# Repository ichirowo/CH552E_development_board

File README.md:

## CH552E development board

This is a development board with [CH552E](http://www.wch-ic.com/products/CH552.html) from Jiangsu Haoheng Co.

It is a multi-functional microcontroller with 4 GPIO pins and supports ADC, PWM, UART, SPI, and USB targets.

LED is connected to P1.4 pin.

A boot button is provided to boot in write mode.

USB TYPE-C connector is used.

If a pin header is attached, it can be used for prototyping on a breadboard.

This board was created with Kicad version 5.1.9.

----

### License

This project is licensed as MIT License.

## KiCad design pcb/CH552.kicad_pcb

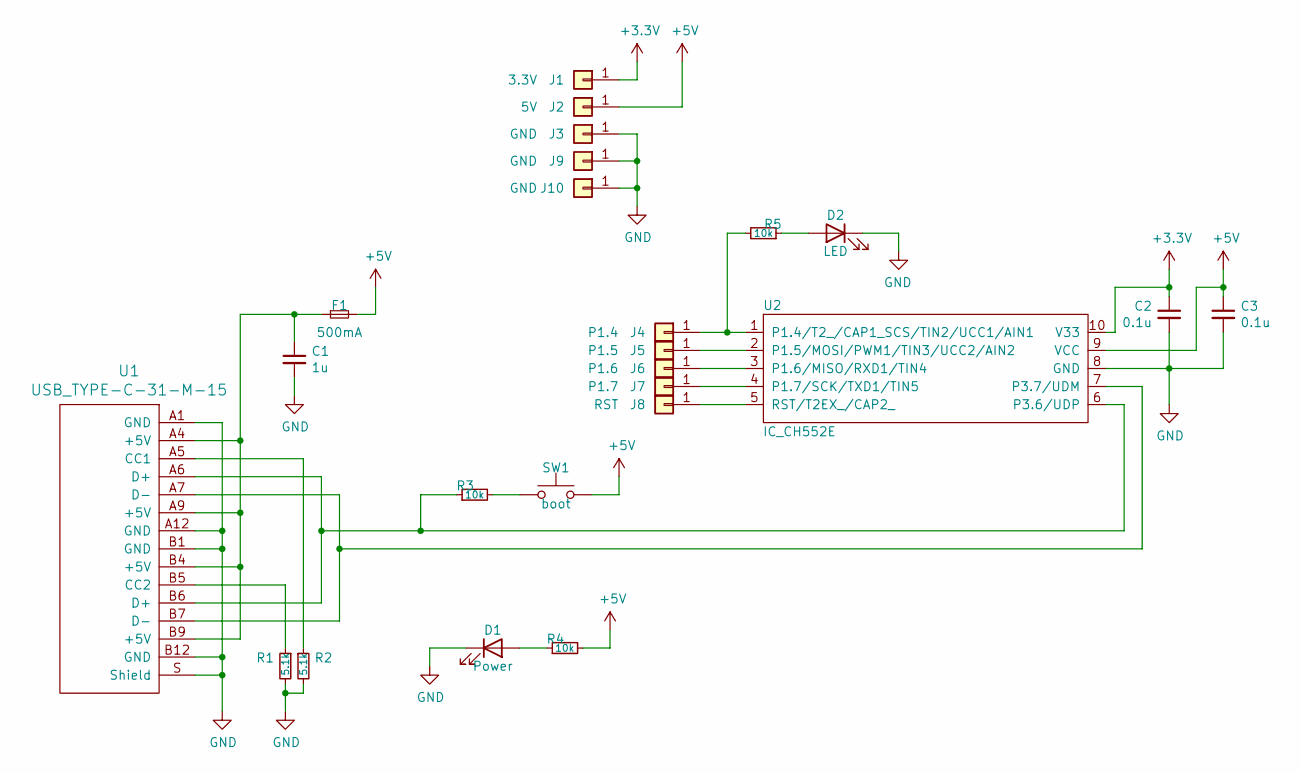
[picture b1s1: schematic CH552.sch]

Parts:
C1: 1u; C_0603_1608Metric_Pad1.05x0.95mm_HandSolder
C2, C3: 0.1u; C_0603_1608Metric_Pad1.05x0.95mm_HandSolder
D1: Power; LED_0603_1608Metric_Pad1.05x0.95mm_HandSolder
D2: LED; LED_0603_1608Metric_Pad1.05x0.95mm_HandSolder
F1: 500mA; Fuse_0603_1608Metric_Pad1.05x0.95mm_HandSolder
J1: 3.3V; Pad_1P_1.9-1.0
J2: 5V; Pad_1P_1.9-1.0
J3, J9, J10: GND; Pad_1P_1.9-1.0
J4: P1.4; Pad_1P_1.9-1.0
J5: P1.5; Pad_1P_1.9-1.0
J6: P1.6; Pad_1P_1.9-1.0
J7: P1.7; Pad_1P_1.9-1.0
J8: RST; Pad_1P_1.9-1.0
R1, R2: 5.1k; R_0603_1608Metric_Pad0.98x0.95mm_HandSolder
R3, R4, R5: 10k; R_0603_1608Metric_Pad0.98x0.95mm_HandSolder
SW1: boot; PTS810_SJM_250_SMTR_LFS
U1: USB_TYPE-C-31-M-15; USB-C_TYPE-C-31-M-12
U2: IC_CH552E; MSOP-10_3x3mm_P0.5mm

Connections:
+3V3: C2.1, J1.1, U2.10 (V33)
+5V: C3.1, F1.2, J2.1, R4.2, SW1.2, U2.9 (VCC)
GND: C1.2, C2.2, C3.2, D1.1 (K), D2.1 (K), J3.1, J9.1, J10.1, R1.2, R2.2, U1.A1 (GND), U1.A12 (GND), U1.B1 (GND), U1.B12 (GND), U1.S (Shield), U2.8 (GND)
unnamed: C1.1, F1.1, U1.A4 (+5V), U1.A9 (+5V), U1.B4 (+5V), U1.B9 (+5V)
unnamed: D1.2 (A), R4.1
unnamed: D2.2 (A), R5.1
unnamed: J4.1, R5.2, U2.1 (P1.4/T2_/CAP1_SCS/TIN2/UCC1/AIN1)
unnamed: J5.1, U2.2 (P1.5/MOSI/PWM1/TIN3/UCC2/AIN2)
unnamed: J6.1, U2.3 (P1.6/MISO/RXD1/TIN4)
unnamed: J7.1, U2.4 (P1.7/SCK/TXD1/TIN5)
unnamed: J8.1, U2.5 (RST/T2EX_/CAP2_)
unnamed: R1.1, U1.B5 (CC2)
unnamed: R2.1, U1.A5 (CC1)
unnamed: R3.1, U1.A6 (D+), U1.B6 (D+), U2.6 (P3.6/UDP)
unnamed: R3.2, SW1.1
unnamed: U1.A7 (D-), U1.B7 (D-), U2.7 (P3.7/UDM)

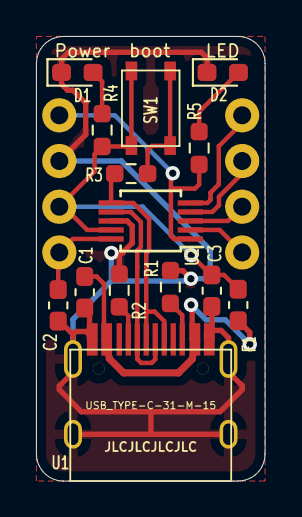
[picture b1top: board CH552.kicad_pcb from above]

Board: 2 copper layers, 12.7 x 24.7 mm, 22 parts (0 on the bottom side), 16 nets.
